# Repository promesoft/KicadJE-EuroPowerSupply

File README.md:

# KicadJE-EuroPowerSupply
Takes a Laptop 19V input and makes +-12 and 5 v out

Please note there is a followup to this repo that has half the width and some fixes: https://github.com/promesoft/KicadJE-EuroPowerSupply2
Please note this method of making +- 12v could be impaired by the laptop PSU ground connection. Some PSU's connect earth to GND (sleeve) which will be connected to -12v and not GND in this circuit.

# MK1 Design
## Status - Installed in Rack
## Initial Unit
| Stage  | Detail | Status |
| ------------- | ------------- | ------------- |
| create material  | sch/pcb | done  |
| | gerber | done |
| production  |   | done |
|  | produced | Done |
|  | delivered | Done |
## Preliminary validation
| Test  | Detail | Status |
| ------------- | ------------- | ------------- |
| Initial Inspection |  | OK |
| Initial Technical Test |   | OK see errata |
| Initial Product Test |   | OK |

## Secondary validation
| Test  | Detail | Status |
| ------------- | ------------- |------------- |
| Product Test |  | OK |
| Quality |  | |
| Long Term Product Test | | Installed in rack  - extended to "EuroPowerCon" via +-13,5v |
| |  | Working fine after 1 year with different modules coming and going |

## Second Unit tests
| Test  | Action | Status |
| ------------- | ------------- |------------- |
| Lower Power Consumption | Bypass Line regulation TIP41 and turn down DCDC to 27v |  |
| Lower Power Consumption | twist the offset of VGND in favor of a Vss = -14v Vcc = -13v |  |
| Simplify | Ommit Banana Jacks | |

## Errata
 * U203 DCDC 5V stepdn converter mirrored pinout - mount on other side (where there is more room)
 * Smaller +28V DCDC does not work - they burn themselves (tried 3 units)
## Issues and Notes
Note - as most powerdraw is on the +12V and +5V side the negative rail is not pulling down the VGND and the TIP42 needs to do all the heavy lifting - resulting in wasting almost 1/2 the power in this transistor.

The TIP41 line regulator passes all the current and the more regulation it needs to perform the more power it wastes and the hotter it gets. Therefore the Zener input should be matched well with the DCDC Boosted output to avoid power wastage.

Another result is a higher Current draw on the primary side, which will blow the input fuse faster. As a result - a powerdraw of 200mA on +12v will result in almost 0,5A on the primary side.

 * Bananas cant be mounted on PCB - too short
 * Consider soft startup current
 * Consider larger drill size for 7812 7805 and 7912
 * Consider cooling of TIP41's and TIP42
 * Blue LED is brighter than RED - Consider 1k for RED +12 470R for RED +5 and 1k5 for BLUE 
### Workarounds
 * U203 DCDC 5V stepdn converter mirrored pinout - mount on other side (where there is more room - and easier adjustment options)

# Base Construction 
The idea is to have a laptop power supply provide the power for the synth, as they are powerful and inexpensive.

## Inputs
19v DC barrel jack.

## Outputs
### Front side
 - Banana +12v
 - Banana +5v
 - Banana GND
 - Banana -12v

### Back side
 - 10 pin doepfer connector
 - 16 pin doepfer connector
 - +/- 12v connector
 - +5 v connector

## Electrical
The input is fed to a DC-DC boost converter (to 30volts) and to a virtual GND circuit (making it +-15v) for the +-12v supply.
The +15v is sent to a step down converter (to 7volts) for the +5v supply.
The +-15 and +7 volt supplies are provided through common mode chokes to linear regulators.

## Regulation and noise 
### Input
No filtering on the input except for the overvoltage protection and  smoothing capacitor after the bridge rectifier.
### DCDC - Boost 30v
Directly on the DCDC output is made room for a Zener regulated NPN for 28 or 30v depending on the boost converter.
The 30v is sent to a Virtual GND that has smoothing capacitors on the input and output.
After the VGND room has been made for either small resistors (forming an RC filter) or a common mode choke for high frequency filtering.
Regulation is performed after the RC / LC filter with linear 7812 / 7912 regulators.

### DCDC - Buck 5v

### Safety / Protection
The 19v is fed through a bridge rectifier to protect the circuit and allow for both AC and DC with any polarity. The circuit is protected on the input by a polyfuse and a VDR afterwards in parallel with a Zener (or TVS) in series w a small resistor to protect from overcurrent, over voltage and spikes.
The linear regulators are fused with polyfuses

## Physical
The product is an 8HP module for the front of a Eurorack synth.

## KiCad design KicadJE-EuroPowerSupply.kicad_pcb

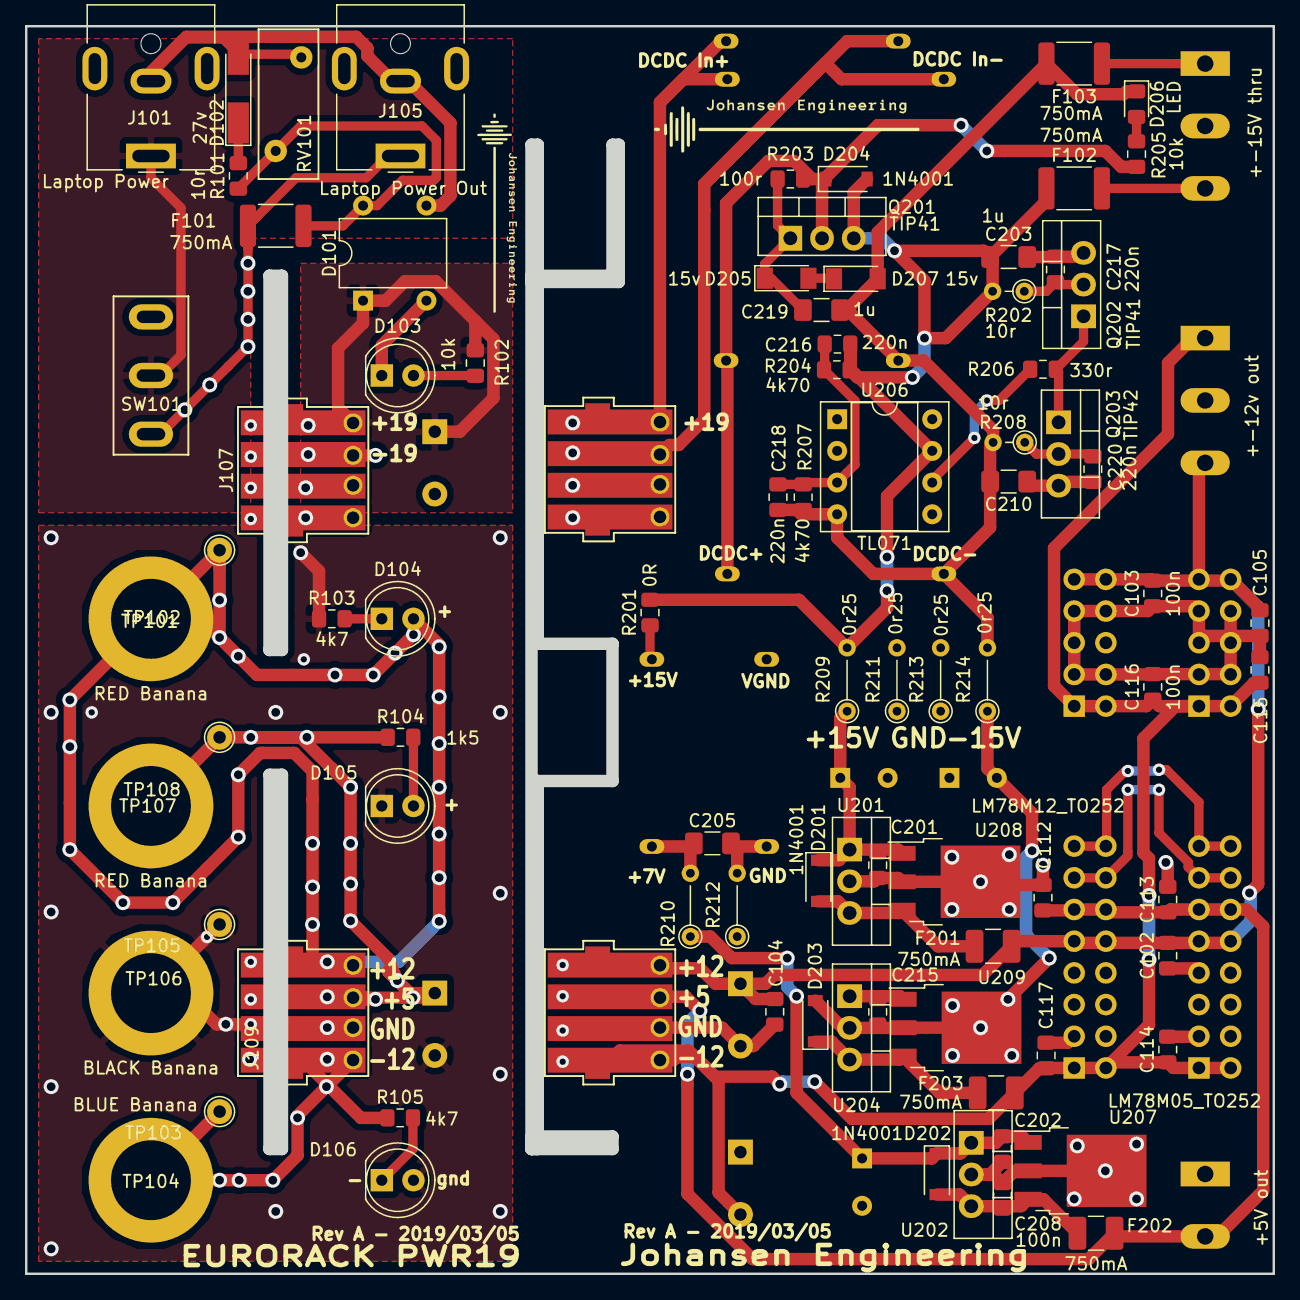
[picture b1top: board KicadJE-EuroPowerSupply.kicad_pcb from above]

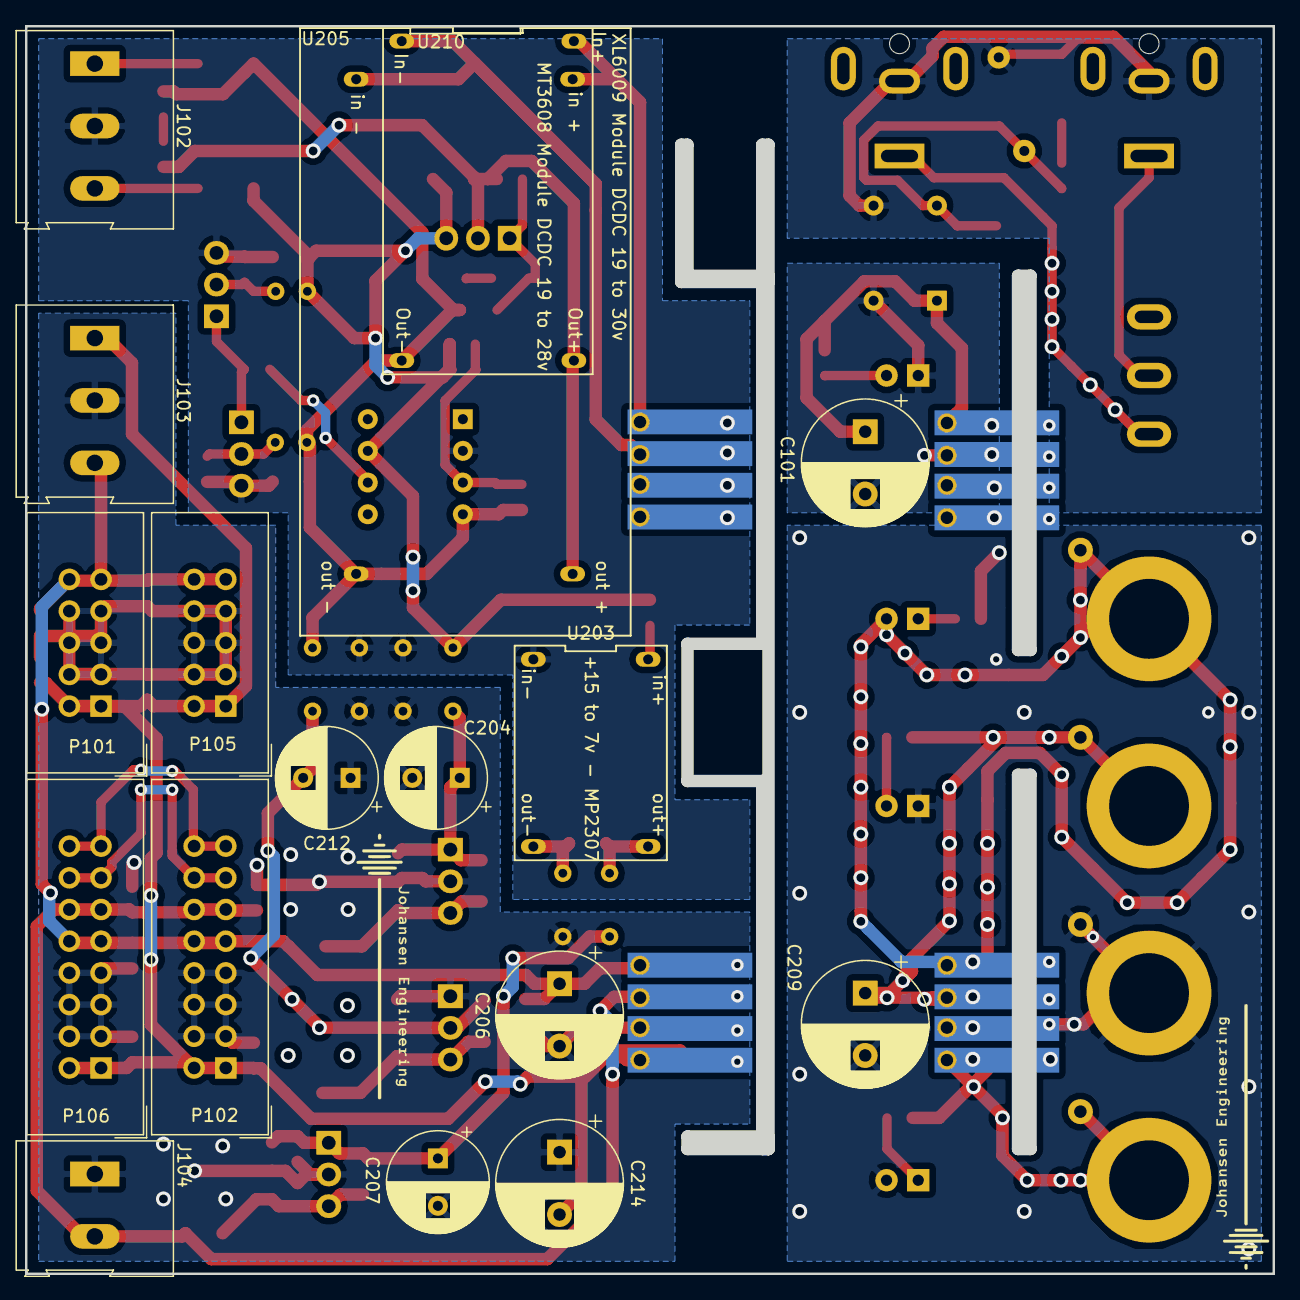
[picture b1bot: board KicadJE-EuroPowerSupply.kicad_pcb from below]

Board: 2 copper layers, 100.0 x 100.0 mm, 103 parts (17 on the bottom side), 40 nets.

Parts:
C101: 100uF; CP_Radial_D10.0mm_P5.00mm
C102, C103, C104, C105, C112, C113, C114, C115, C116, C117, C201, C202, C208, C215: 100n; C_0805_2012Metric_Pad1.15x1.40mm_HandSolder
C203, C205, C210, C219: 1u; C_1206_3216Metric_Pad1.42x1.75mm_HandSolder
C204, C207, C212: 1000uF; CP_Radial_D8.0mm_P3.80mm
C206, C209, C214: 1000uF; CP_Radial_D10.0mm_P5.00mm
C216, C217, C218, C220: 220n; C_0805_2012Metric_Pad1.15x1.40mm_HandSolder
D101: B125C800DM - DB107; Diode_Bridge_DIP-4_W7.62mm_P5.08mm
D102: 27v; D_MiniMELF_Handsoldering
D103: PWR_IN_LED; LED_D5.0mm
D104, D105, D106: LED; LED_D5.0mm
D201, D202, D203, D204: 1N4001; D_SOD-123
D205, D207: 15v; D_MiniMELF
D206: LED; LED_0805_2012Metric_Pad1.15x1.40mm_HandSolder
F101, F102, F103: 750mA; Fuse_1812_4532Metric_Pad1.30x3.40mm_HandSolder
F201, F202, F203: 750mA; Fuse_1210_3225Metric_Pad1.42x2.65mm_HandSolder
J101: Laptop Power; BarrelJack_CUI_PJ-063AH_Horizontal
J102: +-15V thru; TerminalBlock_Altech_AK300-3_P5.00mm
J103: +-12v out; TerminalBlock_Altech_AK300-3_P5.00mm
J104: +5V out; TerminalBlock_Altech_AK300-2_P5.00mm
J105: Laptop Power Out; BarrelJack_CUI_PJ-063AH_Horizontal
J106: FrontInterConnVin; BoardConnector2x2.54x10mm4pin
J107: BaseInterConnVin; BoardConnector2x2.54x10mm4pin
J108: FrontInterConnVout; BoardConnector2x2.54x10mm4pin
J109: BaseInterConnVout; BoardConnector2x2.54x10mm4pin
P101, P105: Doepfer_Power_10pin; IDC-Header_2x05_Pitch2.54mm_Straight
P102, P106: Doepfer_Power_16pin; IDC-Header_2x08_Pitch2.54mm_Straight
Q201, Q202: TIP41; TO-220-3_Vertical
Q203: TIP42; TO-220-3_Vertical
R101: 10r; R_0805_2012Metric_Pad1.15x1.40mm_HandSolder
R102, R205: 10k; R_0805_2012Metric_Pad1.15x1.40mm_HandSolder
R103, R105: 4k7; R_0805_2012Metric_Pad1.15x1.40mm_HandSolder
R104: 1k5; R_0805_2012Metric_Pad1.15x1.40mm_HandSolder
R201: 0R; R_0805_2012Metric_Pad1.15x1.40mm_HandSolder
R202, R208: 10r; R_Axial_DIN0204_L3.6mm_D1.6mm_P2.54mm_Vertical
R203: 100r; R_0805_2012Metric_Pad1.15x1.40mm_HandSolder
R204, R207: 4k70; R_0805_2012Metric_Pad1.15x1.40mm_HandSolder
R206: 330r; R_0805_2012Metric_Pad1.15x1.40mm_HandSolder
R209, R210, R211, R212, R213, R214: 0r25; R_Axial_DIN0204_L3.6mm_D1.6mm_P5.08mm_Vertical
RV101: Varistor; RV_Disc_D12mm_W4.8mm_P7.5mm
SW101: SW_SPDT; SP1MS1
TP101, TP107: RED Sleeve; TestPoint_THTPad_D2.0mm_Drill1.0mm
TP102, TP108: RED Banana; MountingHole_6.4mm_M6_ISO14580_Pad
TP103: BLUE Sleeve; TestPoint_THTPad_D2.0mm_Drill1.0mm
TP104: BLUE Banana; MountingHole_6.4mm_M6_ISO14580_Pad
TP105: BLACK Sleeve; TestPoint_THTPad_D2.0mm_Drill1.0mm
TP106: BLACK Banana; MountingHole_6.4mm_M6_ISO14580_Pad
U201: LM7812_TO220; TO-220-3_Vertical
U202: LM7805_TO220; TO-220-3_Vertical
U203: +15 to 7v - MP2307; MP2307 DCDC module
U204: LM7912_TO220; TO-220-3_Vertical
U205: XL6009 Module DCDC 19 to 30v; XL6009-DCDC-Module
U206: TL071; DIP-8_W7.62mm_Socket
U207: LM78M05_TO252; TO-252-3_TabPin2
U208: LM78M12_TO252; TO-252-3_TabPin2
U209: MC79M12_TO252; TO-252-3_TabPin2
U210: MT3608 Module DCDC 19 to 28v; MT3608 DCDC-Module-USB

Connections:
5Vreg: C208.1, D202.2, F202.1, U202.3, U207.3
12Vreg: D201.2, F201.1, U201.3, U208.3
+5V: C112.1, C113.1, C209.1, F202.2, J104.2, J108.2, J109.2, P102.11, P102.12, P106.11, P106.12, R104.1, TP107.1, TP108.1
+7.5V: C202.1, C207.1, D202.1, R210.1, U202.1, U207.1
+12V: C102.2, C103.2, C104.2, C105.2, C206.1, D104.2, F201.2, J103.3, J108.1, J109.1, P101.9, P101.10, P102.9, P102.10, P105.9, P105.10, P106.9, P106.10, TP101.1, TP102.1
+15V: C201.1, C204.1, D201.1, R209.1, U201.1, U208.1
-12V: C114.1, C115.1, C116.1, C117.1, C214.2, F203.2, J103.1, J108.4, J109.4, P101.1, P101.2, P102.1, P102.2, P105.1, P105.2, P106.1, P106.2, R105.1, TP103.1, TP104.1
-12Vreg: D203.1, F203.1, U204.3, U209.3
-15V: C212.2, C215.2, D203.2, R214.1, U204.2, U209.2
/DCSleeve: D101.3, D102.2, J101.2, J105.2, RV101.2
/VoltageRegulation/7V: C205.1, R210.2, U203.4
/VoltageRegulation/GND-7V: C205.2, R212.2, U203.3
CV: P102.13, P102.14, P106.13, P106.14
DCDC+: D204.1, Q201.2, R203.1, R205.1, U205.4, U210.4
GND: C102.1, C103.1, C104.1, C105.1, C112.2, C113.2, C114.2, C115.2, C116.2, C117.2, C201.2, C202.2, C204.2, C206.2, C207.2, C208.2, C209.2, C212.1, C214.1, C215.1, D105.1, D106.2, J103.2, J104.1, J108.3, J109.3, P101.3, P101.4, P101.5, P101.6, P101.7, P101.8, P102.3, P102.4, P102.5, P102.6, P102.7, P102.8, P105.3, P105.4, P105.5, P105.6, P105.7, P105.8, P106.3, P106.4, P106.5, P106.6, P106.7, P106.8, R103.1, R211.1, R212.1, R213.1, TP105.1, TP106.1, U201.2, U202.2, U204.1, U207.2, U208.2, U209.1
Gate: P102.15, P102.16, P106.15, P106.16
unnamed: C216.2, C218.1, R204.2, R207.1, U206.3
unnamed: C217.1, Q202.2, R202.1
unnamed: C219.1, D205.1, Q201.1, R203.2
unnamed: C220.2, Q203.2, R208.1
unnamed: D101.4, F101.2, R101.1, RV101.1
unnamed: D102.1, R101.2
unnamed: D103.2, R102.2
unnamed: D104.1, R103.2
unnamed: D105.2, R104.2
unnamed: D106.1, R105.2
unnamed: D205.2, D207.1
unnamed: D206.2, R205.2
unnamed: F101.1, J105.1, SW101.1
unnamed: F102.2, J102.3
unnamed: F103.1, J102.1
unnamed: J101.1, SW101.2
unnamed: Q202.1, Q203.1, R206.1
unnamed: R201.1, U203.2
unnamed: R206.2, U206.6
Vin+15: C203.1, C216.1, D204.2, F102.1, Q201.3, R201.2, R202.2, R204.1, R209.2, U206.7
Vin-15: C210.2, C218.2, C219.2, D206.1, D207.2, F103.2, R207.2, R208.2, R214.2, U205.3, U206.4, U210.3
Vin-Neg19: C101.2, D101.2, D103.1, J106.2, J107.2, U205.1, U210.1
Vin-Pos19: C101.1, D101.1, J106.1, J107.1, R102.1, U205.2, U210.2
VinGND: C203.2, C210.1, C217.2, C220.1, J102.2, Q202.3, Q203.3, R211.2, R213.2, U203.1, U206.2

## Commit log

2019-03-04 schematics taking shape
2019-03-05 schematic break up in two sheets
2019-03-05 Linear regulation on 30V DCDC with BJT
2019-03-05 alternative DCDC and replaced XL4005 w XL6009
2019-03-05 Barel jacks footprints
2019-03-05 Front Plate and DXF file created - DXF file imported in PCB
2019-03-05 cut down to 2x10p and 2x16p
2019-03-05 Toroid footprints
2019-03-05 TO252 output fused
2019-03-05 3D Jigzaw started 90degr
2019-03-06 Board interconnect
2019-03-06 Init wiring
2019-03-07 Components placed on PCB - common modes removed
2019-03-07 TP removed - common modes replaced by low ohm resistors
2019-03-07 Initial Route
2019-03-07 3D png
2019-03-07 faceplate text
2019-03-07 gerber
2019-03-07 drill
2019-03-13 Noise filtering
2019-03-23 Create fp-info-cache
2019-04-03 Update README.md
    Power talks
2019-06-04 Update fp-info-cache
2025-01-16 Update README.md
    https://github.com/promesoft/KicadJE-EuroPowerSupply2
2025-01-16 Update README.md
    Please note this method of making +- 12v could be impaired by the laptop PSU ground connection. Some PSU's connect earth to GND (sleeve) which will be connected to -12v and not GND in this circuit.
2025-01-17 Pictures of the completed pcb
